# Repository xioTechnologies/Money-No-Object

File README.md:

Money-No-Object
===============

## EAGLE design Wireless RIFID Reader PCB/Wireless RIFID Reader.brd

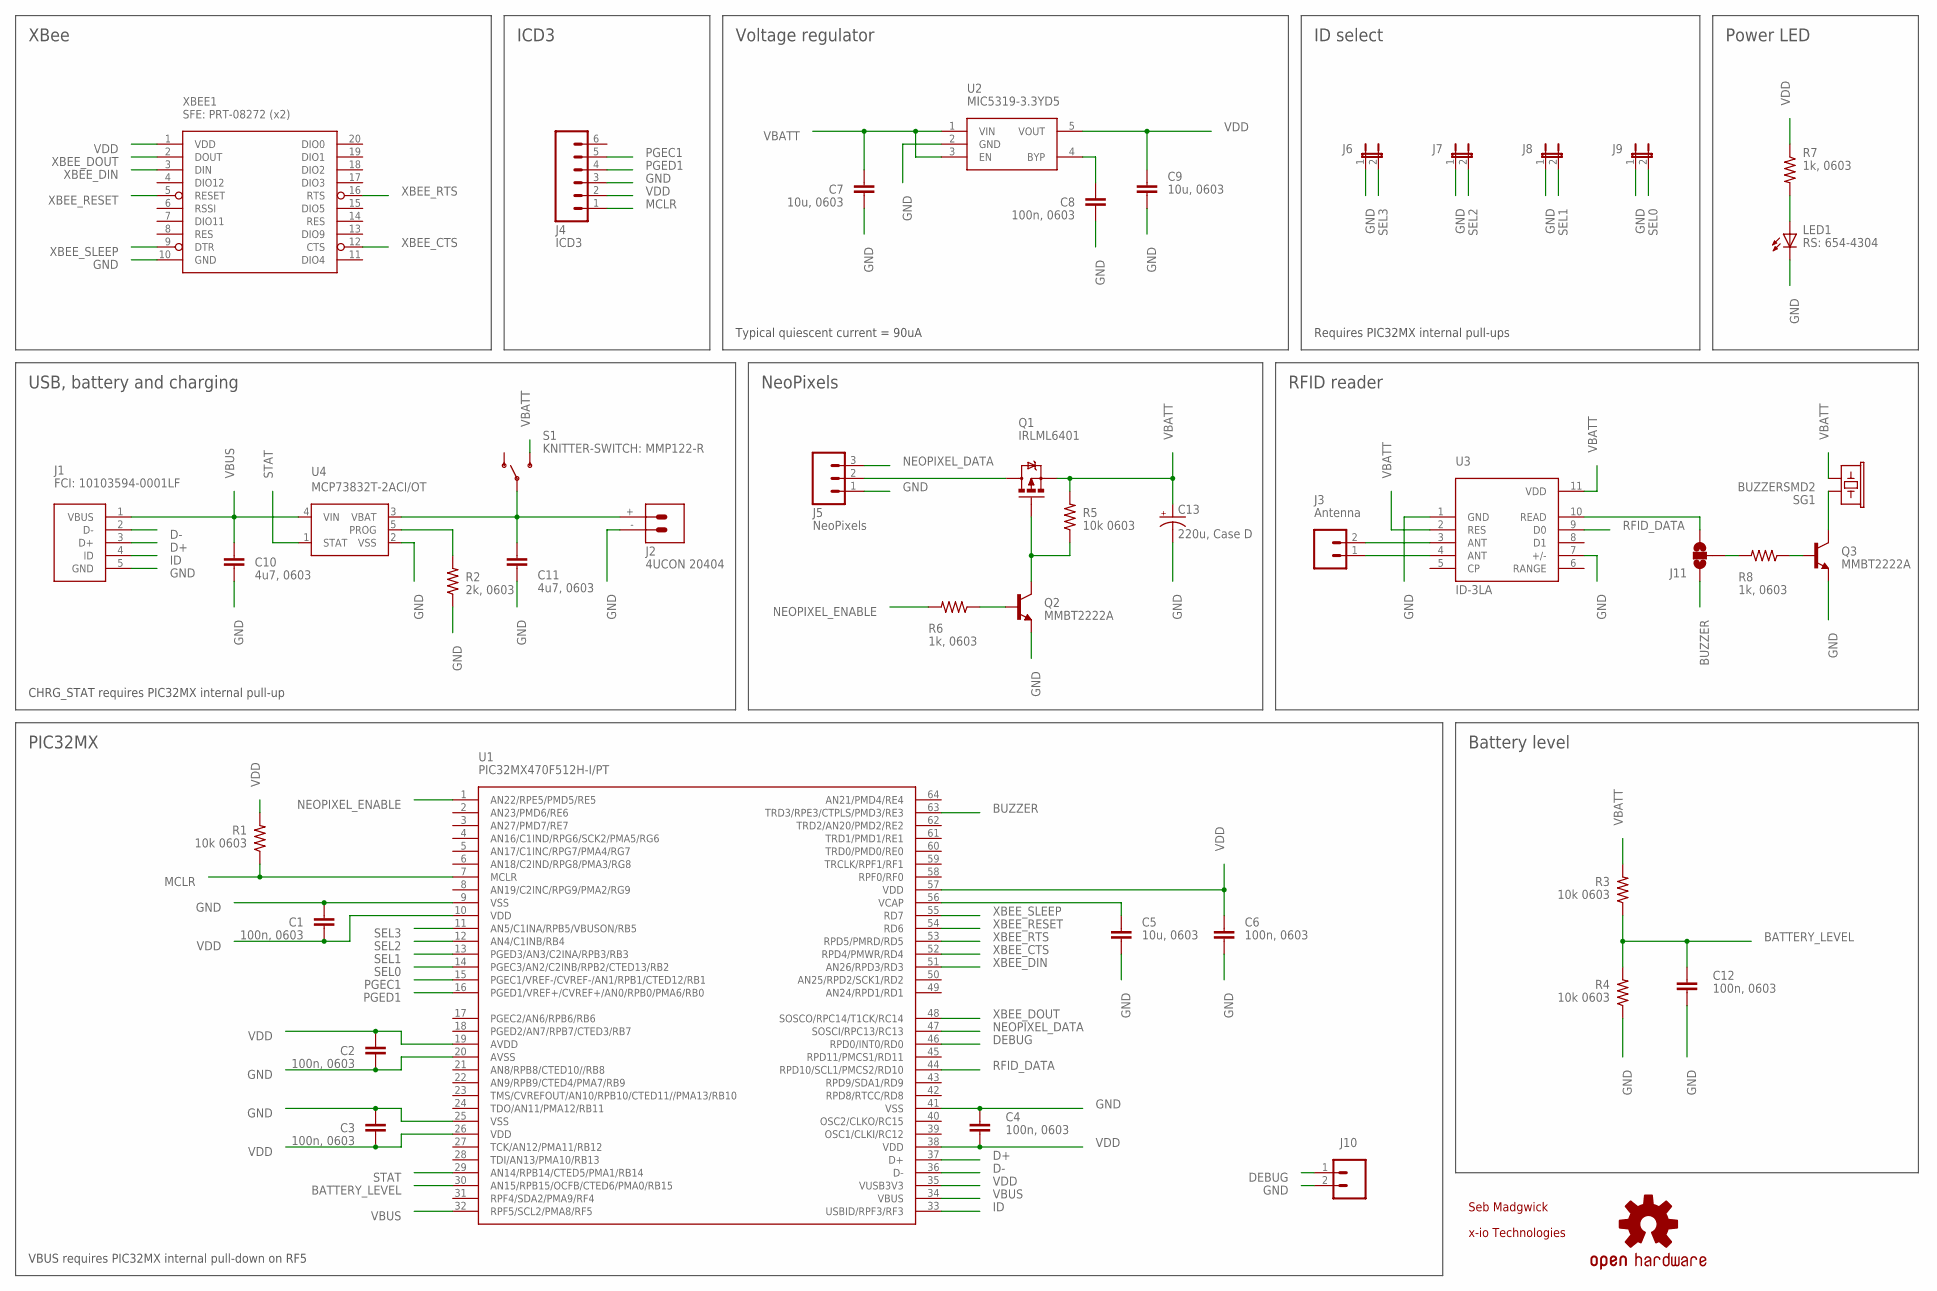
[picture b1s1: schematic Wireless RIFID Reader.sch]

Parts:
C1, C2, C3, C4, C6, C8, C12: 100n, 0603; 0402-CAP
C5, C7, C9: 10u, 0603; 0402-CAP
C10, C11: 4u7, 0603; 0402-CAP
C13: 220u, Case D; SMC_D
J1: FCI: 10103594-0001LF; 10103594-0001LF
J2: 4UCON 20404; JST-R/A
J3: Antenna; 1X02
J4: ICD3; 1X06_NO_SILK
J5: NeoPixels; 1X03
J6, J7, J8, J9: JUMPER-2SMD-NO; SJ_2S-NO
J10: M02PTH; 1X02
J11: JUMPER-PAD-3-NOFULL_BOX_SILK; PAD-JUMPER-3-NO_YES_SILK_FULL_BOX
LED1: RS: 654-4304; LED-0603
LOGO1: OSHW-LOGOM; OSHW-LOGO-M
Q1: IRLML6401; SOT23
Q2, Q3: MMBT2222A; SOT23-3
R1, R3, R4, R5: 10k 0603; 0402-RES
R2: 2k, 0603; 0402-RES
R6, R7, R8: 1k, 0603; 0402-RES
S1: KNITTER-SWITCH: MMP122-R; MMP122-R
SG1: BUZZERSMD2; BUZZER-CCV
U1: PIC32MX470F512H-I/PT; TQFP64-10X10
U2: MIC5319-3.3YD5; SOT23-5
U3: ID-3LA
U4: MCP73832T-2ACI/OT; SOT23-5
XBEE1: SFE: PRT-08272 (x2); XBEE-1

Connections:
BATTERY_LEVEL: C12.1, R3.1, R4.2, U1.30 (AN15/RPB15/OCFB/CTED6/PMA0/RB15)
BUZZER: J11.1, U1.63 (TRD3/RPE3/CTPLS/PMD3/RE3)
D+: J1.3 (D+), U1.37 (D+)
D-: J1.2 (D-), U1.36 (D-)
DEBUG: J10.1, U1.46 (RPD0/INT0/RD0)
GND: C1.1, C2.2, C3.1, C4.1, C5.2, C6.2, C7.2, C8.2, C9.2, C10.2, C11.2, C12.2, C13.-, J1.5 (GND), J2.-, J4.3, J5.1, J6.1, J7.1, J8.1, J9.1, J10.2, LED1.C, Q2.2 (E), Q3.2 (E), R2.1, R4.1, U1.9 (VSS), U1.20 (AVSS), U1.25 (VSS), U1.41 (VSS), U2.2 (GND), U3.1 (GND), U3.7 (+/-), U4.2 (VSS), XBEE1.10 (GND)
ID: J1.4 (ID), U1.33 (USBID/RPF3/RF3)
MCLR: J4.1, R1.1, U1.7 (MCLR)
unnamed: J3.2, U3.3 (ANT)
unnamed: J3.1, U3.4 (ANT)
unnamed: C11.1, J2.+, S1.2, U4.3 (VBAT)
unnamed: J5.2, Q1.3 (D)
unnamed: Q1.1 (G), Q2.3 (C), R5.1
unnamed: Q2.1 (B), R6.1
unnamed: C8.1, U2.4 (BYP)
unnamed: R2.2, U4.5 (PROG)
unnamed: LED1.A, R7.2
unnamed: Q3.1 (B), R8.1
unnamed: C5.1, U1.56 (VCAP)
unnamed: Q3.3 (C), SG1.+ (1)
unnamed: J11.3, U3.10 (READ)
unnamed: J11.2, R8.2
NEOPIXEL_DATA: J5.3, U1.47 (SOSCI/RPC13/RC13)
NEOPIXEL_ENABLE: R6.2, U1.1 (AN22/RPE5/PMD5/RE5)
PGEC1: J4.5, U1.15 (PGEC1/VREF-/CVREF-/AN1/RPB1/CTED12/RB1)
PGED1: J4.4, U1.16 (PGED1/VREF+/CVREF+/AN0/RPB0/PMA6/RB0)
RFID_DATA: U1.44 (RPD10/SCL1/PMCS2/RD10), U3.9 (D0)
SEL0: J9.2, U1.14 (PGEC3/AN2/C2INB/RPB2/CTED13/RB2)
SEL1: J8.2, U1.13 (PGED3/AN3/C2INA/RPB3/RB3)
SEL2: J7.2, U1.12 (AN4/C1INB/RB4)
SEL3: J6.2, U1.11 (AN5/C1INA/RPB5/VBUSON/RB5)
STAT: U1.29 (AN14/RPB14/CTED5/PMA1/RB14), U4.1 (STAT)
VBATT: C7.1, C13.+, Q1.2 (S), R3.2, R5.2, S1.3, SG1.- (2), U2.1 (VIN), U2.3 (EN), U3.2 (RES), U3.11 (VDD)
VBUS: C10.1, J1.1 (VBUS), U1.32 (RPF5/SCL2/PMA8/RF5), U1.34 (VBUS), U4.4 (VIN)
VDD: C1.2, C2.1, C3.2, C4.2, C6.1, C9.1, J4.2, R1.2, R7.1, U1.10 (VDD), U1.19 (AVDD), U1.26 (VDD), U1.35 (VUSB3V3), U1.38 (VDD), U1.57 (VDD), U2.5 (VOUT), XBEE1.1 (VDD)
XBEE_CTS: U1.52 (RPD4/PMWR/RD4), XBEE1.12 (CTS)
XBEE_DIN: U1.51 (AN26/RPD3/RD3), XBEE1.3 (DIN)
XBEE_DOUT: U1.48 (SOSCO/RPC14/T1CK/RC14), XBEE1.2 (DOUT)
XBEE_RESET: U1.54 (RD6), XBEE1.5 (RESET)
XBEE_RTS: U1.53 (RPD5/PMRD/RD5), XBEE1.16 (RTS)
XBEE_SLEEP: U1.55 (RD7), XBEE1.9 (DTR)

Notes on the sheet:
XBee
Battery level
USB, battery and charging
Voltage regulator
CHRG_STAT requires PIC32MX internal pull-up
Seb Madgwick
x-io Technologies
Typical quiescent current = 90uA
PIC32MX
RFID reader
NeoPixels
ID select
Requires PIC32MX internal pull-ups
ICD3
VBUS requires PIC32MX internal pull-down on RF5
Power LED

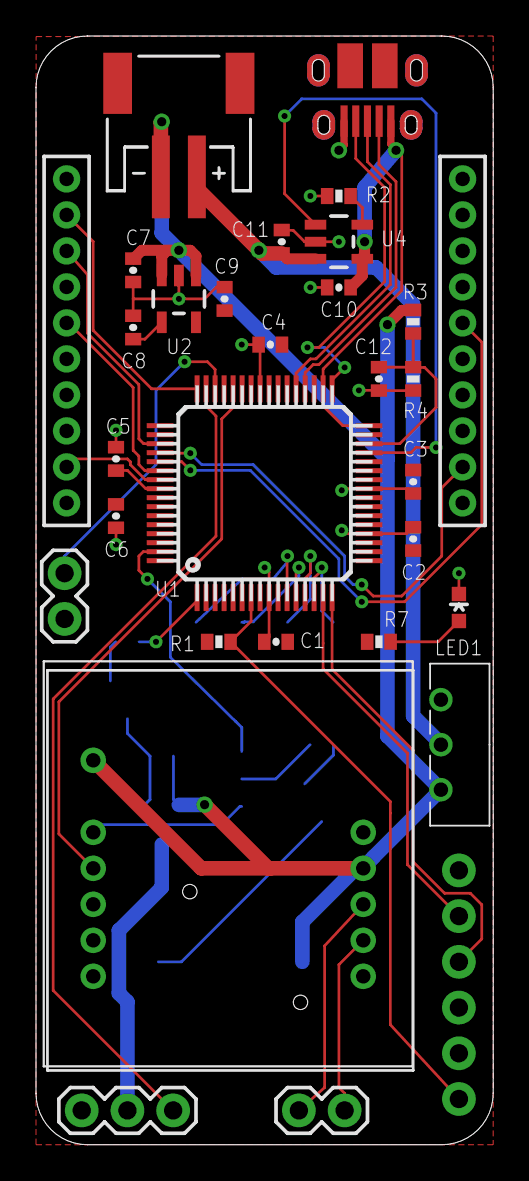
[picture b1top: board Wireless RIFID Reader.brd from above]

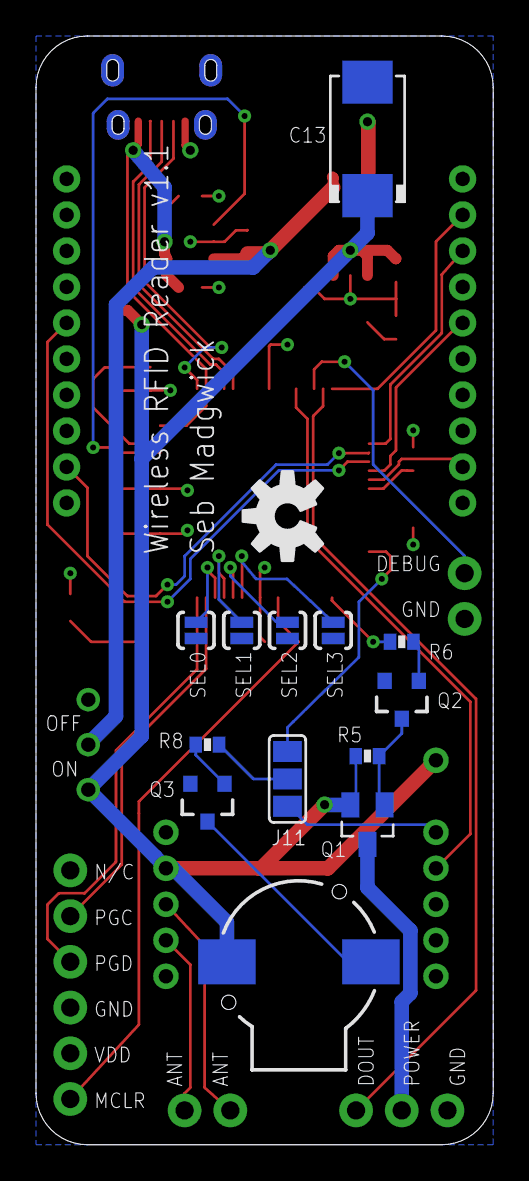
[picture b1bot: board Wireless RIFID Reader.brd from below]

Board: 2 copper layers, 25.4 x 61.6 mm, 44 parts (14 on the bottom side), 41 nets.

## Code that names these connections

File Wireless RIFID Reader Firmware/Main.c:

/*
 * File:   Main.c
 * Author: Seb Madgwick
 *
 * Device:
 * PIC32MX450F256H
 *
 * Compiler:
 * XC32 v1.32
 *
 * Peripherals used:
 * Core timer           Delay.c
 * SPI1                 NeoPixels.c
 * UART1                Uart1.c
 * UART2                Uart2.c
 *
 * Interrupt priorities (nesting enabled):
 * 7. SPI1 (NeoPixels.c)
 * 6.
 * 5.
 * 4.
 * 3. Input change notification (Rfid.c)
 * 2. UART1 (Uart1.c), UART2 (Uart2.c)
 * 1.
 */

//------------------------------------------------------------------------------
// Includes

#include "Animations/Animations.h"
#include "Battery/Battery.h"
#include "DeviceID/DeviceID.h"
#include "FirmwareVersion.h"
#include <plib.h>
#include "Rfid/Rfid.h"
#include "SleepTimer/SleepTimer.h"
#include "SystemClock.h"
#include "NeoPixels/NeoPixels.h"
#include "XBee/XBee.h"

//------------------------------------------------------------------------------
// Configuration Bits

#pragma config FNOSC = FRCPLL // Fast RC Oscillator with divide-by-N with PLL module
#pragma config FPLLMUL = MUL_20, FPLLIDIV = DIV_2, FPLLODIV = DIV_1 // SYSCLK = 80 MHz
#pragma config FSOSCEN = OFF // Disable Secondary Oscillator
#pragma config FWDTEN = OFF // Watchdog Timer is not enabled
#pragma config JTAGEN = OFF // JTAG is disabled
#pragma config ICESEL = ICS_PGx1 // PGEC1/PGED1 pair is used
#pragma config OSCIOFNC = ON // CLKO output signal active on the OSCO pin

//------------------------------------------------------------------------------
// Function declarations

static void Initialise();

//------------------------------------------------------------------------------
// Functions

int main(void) {

    // Initialise PIC32MX
    Initialise();

    // Initialise modules
    DeviceIDInitialise();
    RfidInitialise();
    XBeeInitialise();
    NeoPixelsInitialise();
    BatteryInitialise();
    SleepTimerInitialise();
    AnimiationInitialise();

    // Start up tasks
    {
        SleepTimerReset();
        char string[256];
        sprintf(string, "%d,%s%s,%f\n", DeviceIDGetID(), "Firmware ", FIRMWARE_VERSION, BatteryGetVoltage());
        XBeePutCharArray(string, strlen(string));
        AnimationsPlay();
    }

    // Main loop
    while (TRUE) {

        // Module tasks
        RfidDoTasks();
        XBeeDoTasks();
        SleepTimerDoTasks();
        AnimationsDoTasks();

        // Application tasks
        if (RfidIsGetReady()) {
            SleepTimerReset();
            char rfidString[16];
            RfidIsGetString(rfidString, sizeof (rfidString));
            char string[256];
            sprintf(string, "%d,%s,%f\n", DeviceIDGetID(), rfidString, BatteryGetVoltage());
            XBeePutCharArray(string, strlen(string));
            AnimationsPlay();
        }
    }
}

static void Initialise() {

    // Configure CPU
    SYSTEMConfigPerformance(SYSCLK);
    INTEnableSystemMultiVectoredInt();

    // Configure pull ups/downs
    CNPDFSET = 0x00000020; // RF5 is VBUS
    CNPUBSET = 0x0000403C; // RB2-5 are SEL0-3, RB14 is charger STAT

    // Configure output states
    mPORTDSetBits(BIT_3); // RD3 is XBee DOUT (U1TX)
    mPORTDSetBits(BIT_5); // RD5 is XBee RTS (U1RTS)
    mPORTDSetBits(BIT_6); // RD6 is XBee Reset
    mPORTESetBits(BIT_5); // RE5 is NeoPixels enable
    mPORTCClearBits(BIT_13); // RC13 is NeoPixels DIN (SDO1).  Why is this bit set after reset?

    // Configure I/O directions
    mPORTDSetPinsDigitalOut(BIT_0); // RD0 is external trigger/debugging pin
    mPORTCSetPinsDigitalIn(BIT_14); // RC14 is XBee DOUT (U1RX)
    mPORTDSetPinsDigitalOut(BIT_3); // RD3 is XBee DIN (U1TX)
    mPORTDSetPinsDigitalIn(BIT_4); // RD4 is XBee CTS (U1CTS)
    mPORTDSetPinsDigitalOut(BIT_5); // RD5 is XBee RTS (U1RTS)
    mPORTDSetPinsDigitalOut(BIT_6); // RD6 is XBee Reset
    mPORTDSetPinsDigitalOut(BIT_7); // RD7 is XBee Sleep
    mPORTDSetPinsDigitalIn(BIT_10); // RD10 is ID-3LA (U2RX)
    mPORTESetPinsDigitalOut(BIT_5); // RE5 is NeoPixels enable
    mPORTCSetPinsDigitalOut(BIT_13); // RC13 is NeoPixels DIN (SDO1)
    mPORTBSetPinsAnalogIn(BIT_15); // RB15 is battery level (AN15)
    mPORTFSetPinsDigitalIn(BIT_5); // RF5 is VBUS
    mPORTBSetPinsDigitalIn(BIT_14); // B14 is charger STAT
    mPORTBSetPinsDigitalIn(BIT_2); // RB2 are SEL0
    mPORTBSetPinsDigitalIn(BIT_3); // RB3 are SEL1
    mPORTBSetPinsDigitalIn(BIT_4); // RB4 are SEL2
    mPORTBSetPinsDigitalIn(BIT_5); // RB5 are SEL3

    // Map peripherals
    PPSInput(1, U1RX, RPC14); // RPC14 is XBee DOUT (U1RX)
    PPSOutput(2, RPD3, U1TX); // RPD3 is XBee DIN (U1TX)
    PPSInput(3, U1CTS, RPD4); // RPD4 is XBee CTS (U1CTS)
    PPSOutput(4, RPD5, U1RTS); // RPD5 is XBee RTS (U1RTS)
    PPSInput(1, U2RX, RPD10); // RPD10 is ID-3LA (U2RX)
    PPSOutput(2, RPC13, SDO1); // RPC13 is NeoPixels DIN (SDO1)
}

//------------------------------------------------------------------------------
// End of file

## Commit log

2014-07-08 Add PCB files
2014-07-17 Commit PCB v1.1 files
2014-08-11 Add RFID Coil Jig files
2014-08-12 Add Wireless RIFID Reader Console files
2014-08-12 Organise directory
2014-08-15 Commit firmware v1.0 files
2014-09-17 Commit v1.1

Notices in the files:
parts and their libraries:
SparkFun-Connectors: Licensing: Creative Commons ShareAlike 4.0 International - https://creativecommons.org/licenses/by-sa/4.0
